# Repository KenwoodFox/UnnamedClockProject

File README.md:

# UnnamedClockProject

This repo contains all the firmware and hardware for the UnnamedClockProject.

If you're looking for the latest docs/builds, see our [Releases Page](https://github.com/KenwoodFox/UnnamedClockProject/releases).

# Getting Started

First, clone this repo (and optionally checkout a branch)

```shell
git clone https://github.com/KenwoodFox/UnnamedClockProject.git
cd UnnamedClockProject
git checkout new_board
```

# Init Submodules

Some libraries and resources are included as submodules, run the following
command to initialize them before opening the main sch

(If you get a missing library error, make sure to do this)

```shell
git submodule update --init --recursive
```

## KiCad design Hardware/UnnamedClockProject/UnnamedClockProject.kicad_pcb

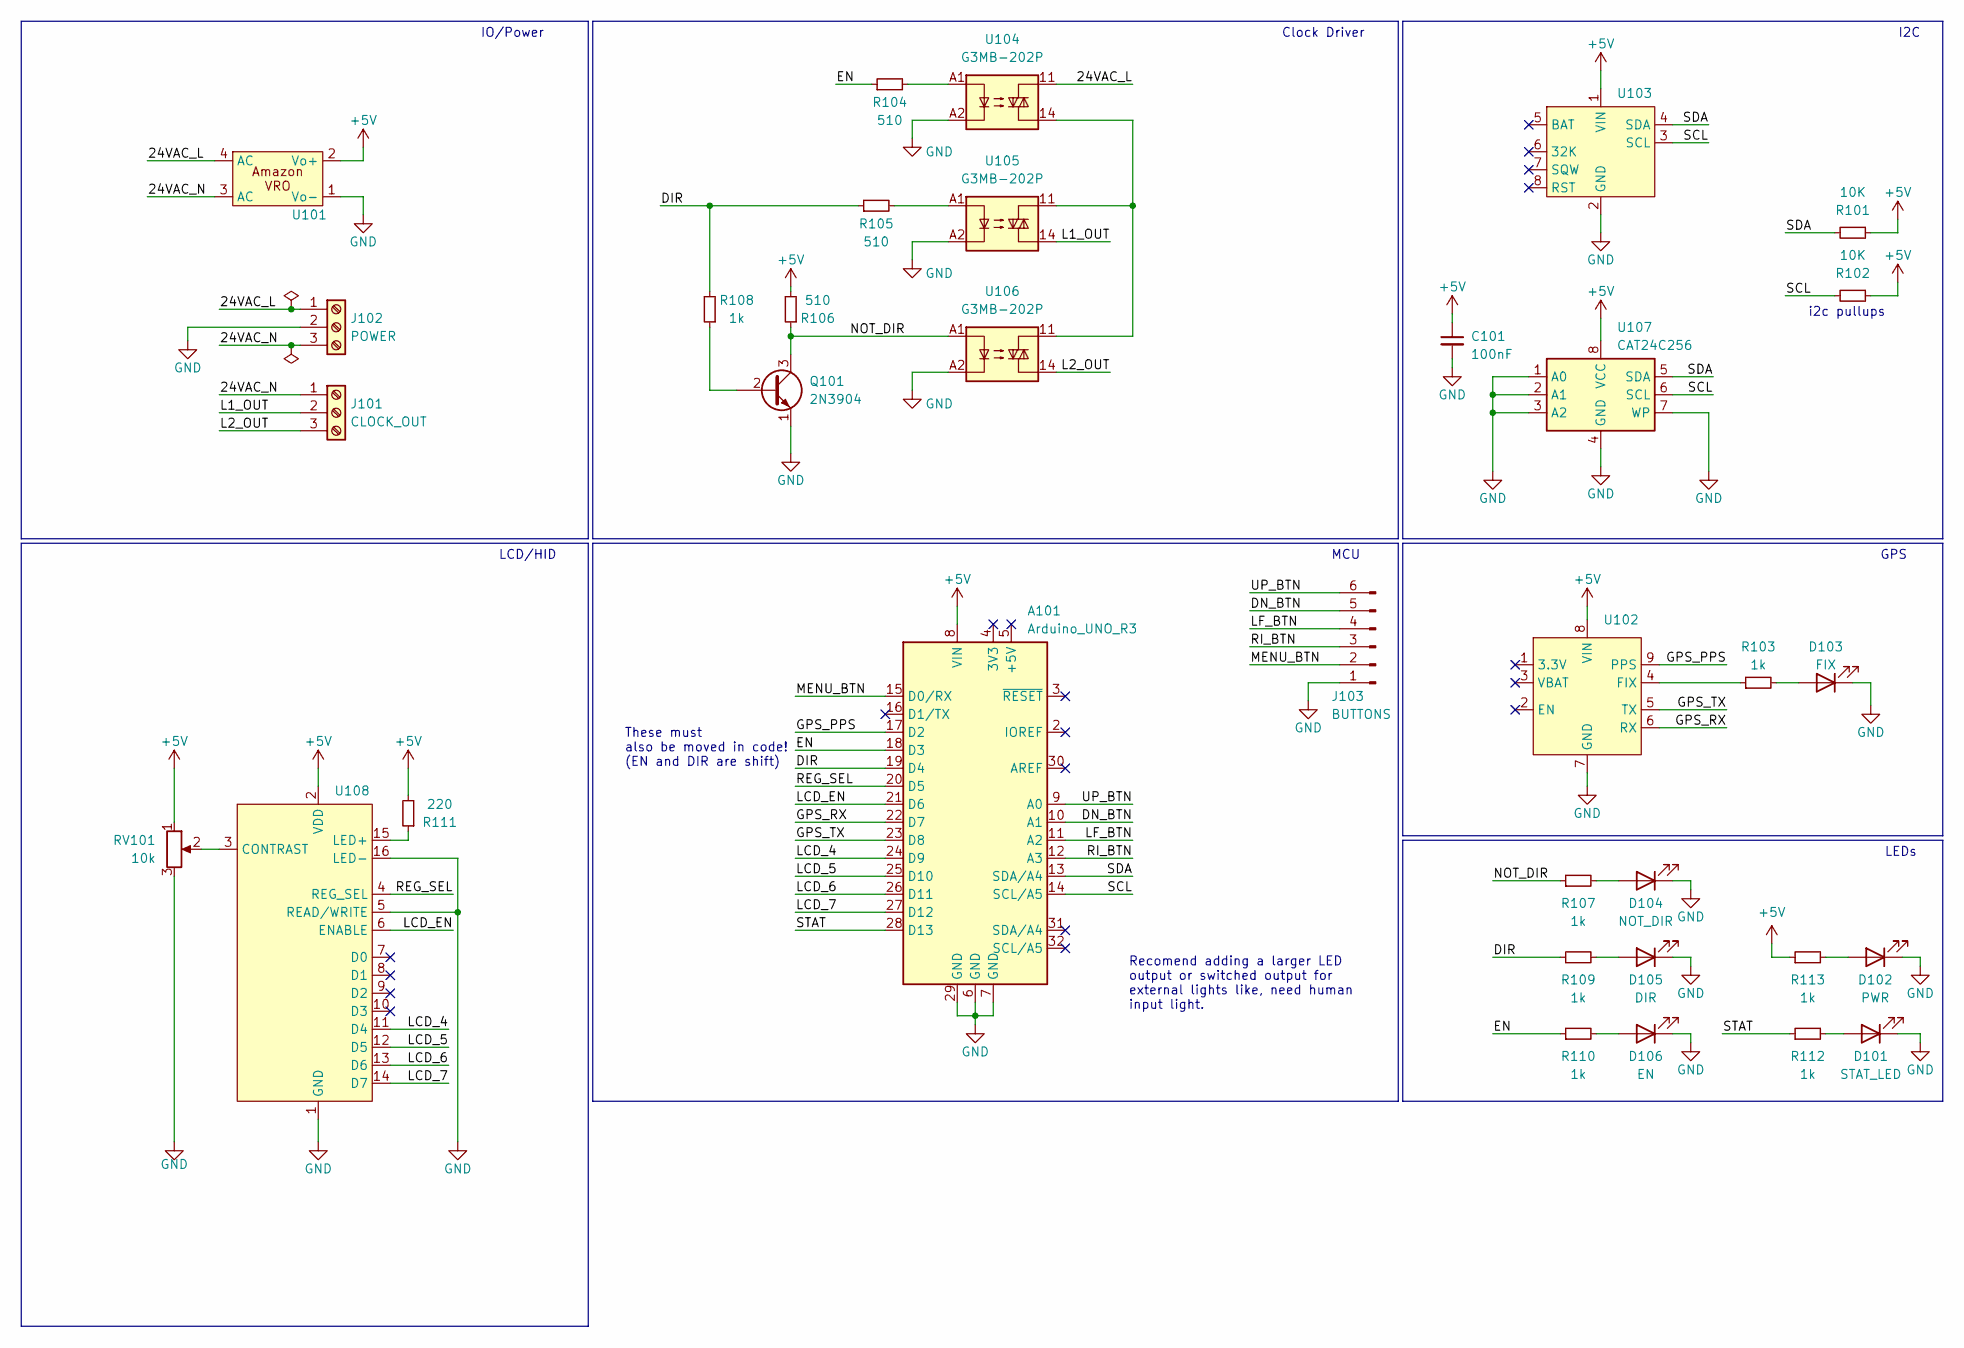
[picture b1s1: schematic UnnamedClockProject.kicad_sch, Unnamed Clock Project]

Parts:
A101: Arduino_UNO_R3; Arduino_Uno_Nano_Combo
C101: 100nF; C_Disc_D5.0mm_W2.5mm_P5.00mm
D101: STAT_LED; LED_D5.0mm
D102: PWR; LED_D5.0mm
D103: FIX; LED_D5.0mm
D104: NOT_DIR; LED_D5.0mm
D105: DIR; LED_D5.0mm
D106: EN; LED_D5.0mm
J101: CLOCK_OUT; TerminalBlock_Phoenix_MKDS-1,5-3_1x03_P5.00mm_Horizontal
J102: POWER; TerminalBlock_Phoenix_MKDS-1,5-3_1x03_P5.00mm_Horizontal
J103: BUTTONS; JST_EH_B6B-EH-A_1x06_P2.50mm_Vertical
Q101: 2N3904; TO-92_Inline
R101, R102: 10K; R_Axial_DIN0207_L6.3mm_D2.5mm_P10.16mm_Horizontal
R103, R107, R108, R109, R110, R112, R113: 1k; R_Axial_DIN0207_L6.3mm_D2.5mm_P10.16mm_Horizontal
R104, R105, R106: 510; R_Axial_DIN0207_L6.3mm_D2.5mm_P10.16mm_Horizontal
R111: 220; R_Axial_DIN0207_L6.3mm_D2.5mm_P10.16mm_Horizontal
RV101: 10k; Potentiometer_Runtron_RM-065_Vertical
U101: Amazon_DRO
U102: Ultimate GPS Breakout V3 Module
U103: DS3231
U104, U105, U106: G3MB-202P; OptoRelay
U107: CAT24C256; DIP-8_W7.62mm
U108: 2x16_LCD

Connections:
+5V: A101.8 (VIN), C101.1, R101.1, R102.1, R106.2, R111.2, R113.1, RV101.1, U101.2 (Vo+), U102.8 (VIN), U103.1 (VIN), U107.8 (VCC), U108.2 (VDD)
/24VAC_L: J102.1, U101.4 (AC), U104.11
/24VAC_N: J101.1, J102.3, U101.3 (AC)
/DIR: A101.19 (D4), R105.1, R108.2, R109.1
/DN_BTN: A101.10 (A1), J103.5
/EN: A101.18 (D3), R104.1, R110.1
/GPS_PPS: A101.17 (D2), U102.9 (PPS)
/GPS_RX: A101.22 (D7), U102.6 (RX)
/GPS_TX: A101.23 (D8), U102.5 (TX)
/L1_OUT: J101.2, U105.14
/L2_OUT: J101.3, U106.14
/LCD_4: A101.24 (D9), U108.11 (D4)
/LCD_5: A101.25 (D10), U108.12 (D5)
/LCD_6: A101.26 (D11), U108.13 (D6)
/LCD_7: A101.27 (D12), U108.14 (D7)
/LCD_EN: A101.21 (D6), U108.6 (ENABLE)
/LF_BTN: A101.11 (A2), J103.4
/MENU_BTN: A101.15 (D0/RX), J103.2
/NOT_DIR: Q101.3 (C), R106.1, R107.1, U106.A1
/REG_SEL: A101.20 (D5), U108.4 (REG_SEL)
/RI_BTN: A101.12 (A3), J103.3
/SCL: A101.14 (SCL/A5), R102.2, U103.3 (SCL), U107.6 (SCL)
/SDA: A101.13 (SDA/A4), R101.2, U103.4 (SDA), U107.5 (SDA)
/STAT: A101.28 (D13), R112.1
/UP_BTN: A101.9 (A0), J103.6
GND: A101.6 (GND), A101.7 (GND), A101.29 (GND), C101.2, D101.1 (K), D102.1 (K), D103.1 (K), D104.1 (K), D105.1 (K), D106.1 (K), J102.2, J103.1, Q101.1 (E), RV101.3, U101.1 (Vo-), U102.7 (GND), U103.2 (GND), U104.A2, U105.A2, U106.A2, U107.1 (A0), U107.2 (A1), U107.3 (A2), U107.4 (GND), U107.7 (WP), U108.1 (GND), U108.5 (READ/WRITE), U108.16 (LED-)
unnamed: D101.2 (A), R112.2
unnamed: D102.2 (A), R113.2
unnamed: D103.2 (A), R103.2
unnamed: D104.2 (A), R107.2
unnamed: D105.2 (A), R109.2
unnamed: D106.2 (A), R110.2
unnamed: Q101.2 (B), R108.1
unnamed: R104.2, U104.A1
unnamed: R105.2, U105.A1
unnamed: R103.1, U102.4 (FIX)
unnamed: U104.14, U105.11, U106.11
unnamed: RV101.2, U108.3 (CONTRAST)
unnamed: R111.1, U108.15 (LED+)

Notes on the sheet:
GPS
These must also be moved in code! (EN and DIR are shift)
Clock Driver
LCD/HID
IO/Power
MCU
Recomend adding a larger LED output or switched output for external lights like, need human input light.
LEDs
i2c pullups
I2C

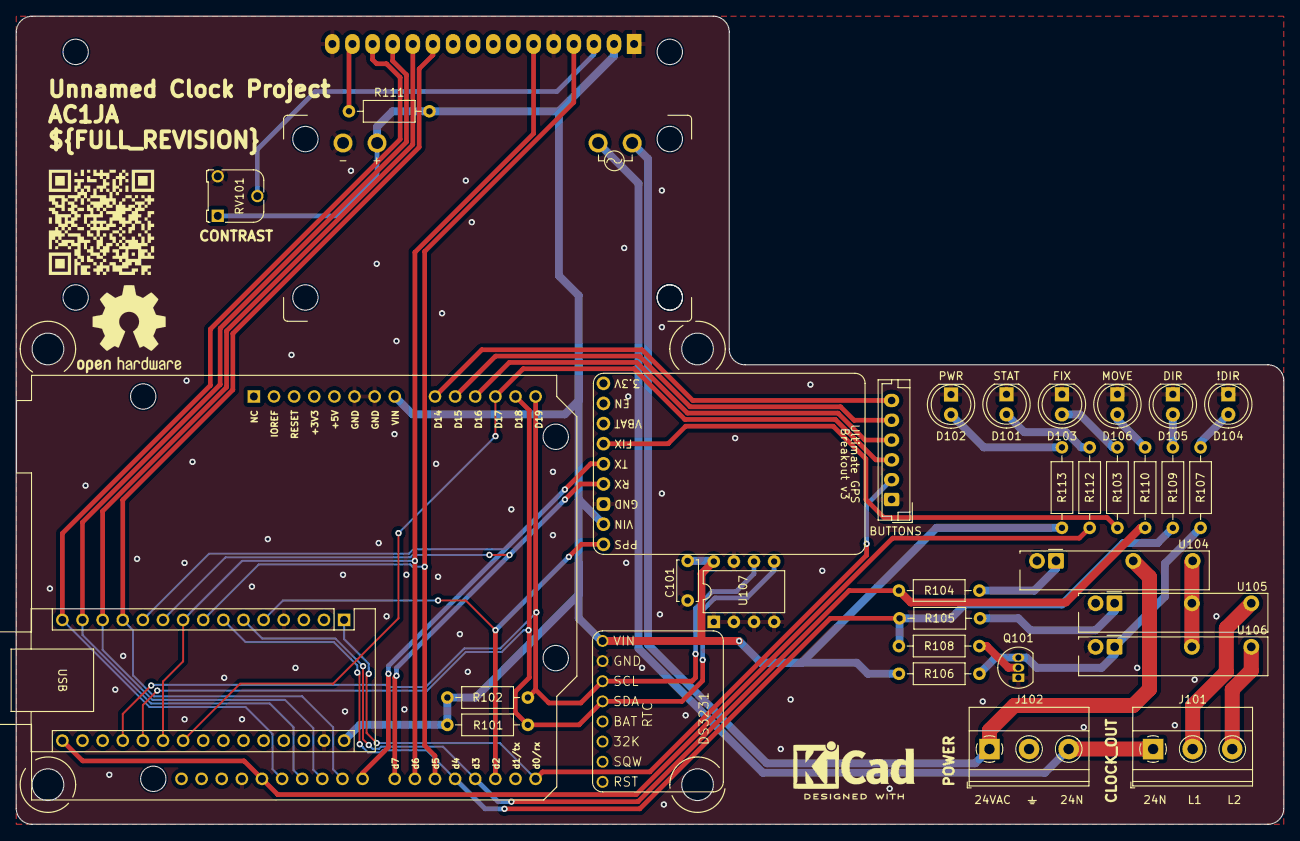
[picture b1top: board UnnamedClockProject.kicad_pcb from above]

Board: 2 copper layers, 160.0 x 102.0 mm, 34 parts (1 on the bottom side), 39 nets.

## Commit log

2023-09-05 Import from cookiecutter https://github.com/KenwoodFox/Project-Template
2023-09-05 Import half baked code
2023-09-05 Import new from template
2023-09-05 Add basics
2023-09-07 Bump upstream libs
2023-09-07 Inital layout
2023-09-07 More boilerplate
2023-09-08 Add new design with solid state relays
2023-09-08 Bump flags, communicate with GPS, lay outline
2023-09-08 Add todo
2023-09-08 Bump hardware version
2023-09-08 Add footprints
2023-09-08 Add plugs
2023-09-08 Tie into mcu
2023-09-11 Add lcd from upstream
2023-09-11 Basics
2023-09-11 Add in new tasks
2023-09-11 fix ERC
2023-09-11 Experiment dev publish
2023-09-11 just see if this works
2023-09-11 bump
2023-09-12 Make build_flags.py portable
2023-09-12 Add inital code for LCD
2023-09-12 Add LCD handling task
2023-09-13 Include suggestion from https://github.com/edunad/actions-image/issues/7\#issuecomment-1715224496
2023-09-13 Add permissions from here https://github.com/edunad/actions-image/blob/4199cf1baa40e6ac5bb71bae6ef55c3801545c01/README.md\?plain\=1\#L12-L17
2023-09-14 add basic GPS wait in LCD task
    Also noticed a possible stack bug where chip would constantly reset if too many calls to LCD print?
2023-09-15 A good spot to start on menus
2023-09-15 Add first menus
2023-09-15 Add third menu:
2023-09-18 Add cad for hands
2023-09-18 Printed
2023-09-18 Move memory buff
2023-09-19 currently working
2023-09-19 GPS runs stable but LCD does not
2023-09-19 Stable here
2023-09-19 Add last bits of clock baseline
2023-09-21 stable here, consider making sleeper task just for clock driver and another for misc?
2023-09-21 Advance code
2023-09-22 Add prev, advance to clock set
2023-09-22 BASIC (and not complete) eeprom
2023-09-22 Better catch up code
2023-09-22 include improvements in upstream template
2023-09-26 Testing
2023-09-26 All tests pass
2023-09-26 Tests look good and new clock hands are being printed
2023-09-29 Better hands and updated clock code
2023-10-01 Add comments
2023-10-02 Add notes
2023-10-03 boilerplate new pcb
2023-10-05 Got some work done on pcb
2023-10-05 Knock out a little more before class
2023-10-07 Complete mounting
2023-10-07 Add amazon dro from upstream, fix logos and prep for RC2
2023-10-07 clean silk and other misc
2023-10-07 shift silk
2023-10-07 RTOS layout and first tasks (#2)
    Code here is stable, and testable. But features are still missing.
    We've submitted the v0.1 board design, so its time to refine the code.
2023-10-07 Stable Firmware (#4)
2023-10-10 Add 3d models
2023-10-10 Change mounting hole size
2023-10-10 Boilerplate new file upstream
2023-10-10 Add bezel
2023-10-14 Update board pins from pcb file
2023-10-15 bump manual override
2023-10-15 Upstream
2023-10-15 Do not track locks
2023-10-15 Fix mounting holes (#7)
2023-10-15 Merge
2023-10-16 Clear movement enabled
2023-10-16 Pushing the memory limits
2023-10-16 Functional here
2023-10-16 Memory limitations (again)
2023-10-16 Add SIMPLE super low memory timezone converter
2023-10-16 Respect movement lockout
2023-10-19 Fix tests
2023-10-19 Bump makefile
2023-10-20 Bump time per
2023-10-20 Increase delay time when moving clock
2023-10-20 add methods to set and unset lefthandedness
2023-10-20 Implement left handed
2023-10-20 Tie settings into buttons
2023-10-20 Timezone Handling and More (#10)
    This PR is ballooning, and too many other prs depend on it. im breaking it up into smaller chunks
2023-10-20 Include upstream libs
2023-10-20 Fix optorelays not fitting (#8)
    This is fine for now, merging mostly because so many code improvements now depend on this branch!
2023-10-20 Re-introduce r4 port
2023-10-21 Fix build (with no tasks obvio)
2023-10-21 add new bezel
2023-10-21 Fix bug in manual mode
2023-10-21 Looking way more promising!
2023-10-21 Move opto back
2023-10-21 Patch breaks compatability but seems to compile!
2023-10-24 Revert back to desk
2023-10-24 add methods to set and unset lefthandedness (#14)
2023-10-26 Super strip
2023-10-26 Slim
